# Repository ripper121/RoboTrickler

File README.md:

# RoboTrickler
 
If you like it, spend me a coffee :)

### Donation: [Paypal](https://www.paypal.com/donate/?hosted_button_id=UHZEEUSTRAF88) (paypal.me/ripper121)

### Full Manual: [Wiki](https://github.com/ripper121/RoboTrickler/wiki)

At the moment only in German, but DeepL will help you ;)

### Latest Release: [Download](https://github.com/ripper121/RoboTrickler/releases/latest)

Youtube:

# License

## creative commons

# Attribution-NonCommercial-ShareAlike 4.0 International

Creative Commons Corporation (“Creative Commons”) is not a law firm and does not provide legal services or legal advice. Distribution of Creative Commons public licenses does not create a lawyer-client or other relationship. Creative Commons makes its licenses and related information available on an “as-is” basis. Creative Commons gives no warranties regarding its licenses, any material licensed under their terms and conditions, or any related information. Creative Commons disclaims all liability for damages resulting from their use to the fullest extent possible.

### Using Creative Commons Public Licenses

Creative Commons public licenses provide a standard set of terms and conditions that creators and other rights holders may use to share original works of authorship and other material subject to copyright and certain other rights specified in the public license below. The following considerations are for informational purposes only, are not exhaustive, and do not form part of our licenses.

* __Considerations for licensors:__ Our public licenses are intended for use by those authorized to give the public permission to use material in ways otherwise restricted by copyright and certain other rights. Our licenses are irrevocable. Licensors should read and understand the terms and conditions of the license they choose before applying it. Licensors should also secure all rights necessary before applying our licenses so that the public can reuse the material as expected. Licensors should clearly mark any material not subject to the license. This includes other CC-licensed material, or material used under an exception or limitation to copyright. [More considerations for licensors](http://wiki.creativecommons.org/Considerations_for_licensors_and_licensees#Considerations_for_licensors).

* __Considerations for the public:__ By using one of our public licenses, a licensor grants the public permission to use the licensed material under specified terms and conditions. If the licensor’s permission is not necessary for any reason–for example, because of any applicable exception or limitation to copyright–then that use is not regulated by the license. Our licenses grant only permissions under copyright and certain other rights that a licensor has authority to grant. Use of the licensed material may still be restricted for other reasons, including because others have copyright or other rights in the material. A licensor may make special requests, such as asking that all changes be marked or described. Although not required by our licenses, you are encouraged to respect those requests where reasonable. [More considerations for the public](http://wiki.creativecommons.org/Considerations_for_licensors_and_licensees#Considerations_for_licensees).

## Creative Commons Attribution-NonCommercial-ShareAlike 4.0 International Public License

By exercising the Licensed Rights (defined below), You accept and agree to be bound by the terms and conditions of this Creative Commons Attribution-NonCommercial-ShareAlike 4.0 International Public License ("Public License"). To the extent this Public License may be interpreted as a contract, You are granted the Licensed Rights in consideration of Your acceptance of these terms and conditions, and the Licensor grants You such rights in consideration of benefits the Licensor receives from making the Licensed Material available under these terms and conditions.

### Section 1 – Definitions.

a. __Adapted Material__ means material subject to Copyright and Similar Rights that is derived from or based upon the Licensed Material and in which the Licensed Material is translated, altered, arranged, transformed, or otherwise modified in a manner requiring permission under the Copyright and Similar Rights held by the Licensor. For purposes of this Public License, where the Licensed Material is a musical work, performance, or sound recording, Adapted Material is always produced where the Licensed Material is synched in timed relation with a moving image.

b. __Adapter's License__ means the license You apply to Your Copyright and Similar Rights in Your contributions to Adapted Material in accordance with the terms and conditions of this Public License.

c. __BY-NC-SA Compatible License__ means a license listed at [creativecommons.org/compatiblelicenses](http://creativecommons.org/compatiblelicenses), approved by Creative Commons as essentially the equivalent of this Public License.

d. __Copyright and Similar Rights__ means copyright and/or similar rights closely related to copyright including, without limitation, performance, broadcast, sound recording, and Sui Generis Database Rights, without regard to how the rights are labeled or categorized. For purposes of this Public License, the rights specified in Section 2(b)(1)-(2) are not Copyright and Similar Rights.

e. __Effective Technological Measures__ means those measures that, in the absence of proper authority, may not be circumvented under laws fulfilling obligations under Article 11 of the WIPO Copyright Treaty adopted on December 20, 1996, and/or similar international agreements.

f. __Exceptions and Limitations__ means fair use, fair dealing, and/or any other exception or limitation to Copyright and Similar Rights that applies to Your use of the Licensed Material.

g. __License Elements__ means the license attributes listed in the name of a Creative Commons Public License. The License Elements of this Public License are Attribution, NonCommercial, and ShareAlike.

h. __Licensed Material__ means the artistic or literary work, database, or other material to which the Licensor applied this Public License.

i. __Licensed Rights__ means the rights granted to You subject to the terms and conditions of this Public License, which are limited to all Copyright and Similar Rights that apply to Your use of the Licensed Material and that the Licensor has authority to license.

j. __Licensor__ means the individual(s) or entity(ies) granting rights under this Public License.

k. __NonCommercial__ means not primarily intended for or directed towards commercial advantage or monetary compensation. For purposes of this Public License, the exchange of the Licensed Material for other material subject to Copyright and Similar Rights by digital file-sharing or similar means is NonCommercial provided there is no payment of monetary compensation in connection with the exchange.

l. __Share__ means to provide material to the public by any means or process that requires permission under the Licensed Rights, such as reproduction, public display, public performance, distribution, dissemination, communication, or importation, and to make material available to the public including in ways that members of the public may access the material from a place and at a time individually chosen by them.

m. __Sui Generis Database Rights__ means rights other than copyright resulting from Directive 96/9/EC of the European Parliament and of the Council of 11 March 1996 on the legal protection of databases, as amended and/or succeeded, as well as other essentially equivalent rights anywhere in the world.

n. __You__ means the individual or entity exercising the Licensed Rights under this Public License. Your has a corresponding meaning.

### Section 2 – Scope.

a. ___License grant.___

   1. Subject to the terms and conditions of this Public License, the Licensor hereby grants You a worldwide, royalty-free, non-sublicensable, non-exclusive, irrevocable license to exercise the Licensed Rights in the Licensed Material to:

        A. reproduce and Share the Licensed Material, in whole or in part, for NonCommercial purposes only; and

        B. produce, reproduce, and Share Adapted Material for NonCommercial purposes only.

   2. __Exceptions and Limitations.__ For the avoidance of doubt, where Exceptions and Limitations apply to Your use, this Public License does not apply, and You do not need to comply with its terms and conditions.

   3. __Term.__ The term of this Public License is specified in Section 6(a).

   4. __Media and formats; technical modifications allowed.__ The Licensor authorizes You to exercise the Licensed Rights in all media and formats whether now known or hereafter created, and to make technical modifications necessary to do so. The Licensor waives and/or agrees not to assert any right or authority to forbid You from making technical modifications necessary to exercise the Licensed Rights, including technical modifications necessary to circumvent Effective Technological Measures. For purposes of this Public License, simply making modifications authorized by this Section 2(a)(4) never produces Adapted Material.

   5. __Downstream recipients.__

        A. __Offer from the Licensor – Licensed Material.__ Every recipient of the Licensed Material automatically receives an offer from the Licensor to exercise the Licensed Rights under the terms and conditions of this Public License.

        B. __Additional offer from the Licensor – Adapted Material.__ Every recipient of Adapted Material from You automatically receives an offer from the Licensor to exercise the Licensed Rights in the Adapted Material under the conditions of the Adapter’s License You apply.

        C. __No downstream restrictions.__ You may not offer or impose any additional or different terms or conditions on, or apply any Effective Technological Measures to, the Licensed Material if doing so restricts exercise of the Licensed Rights by any recipient of the Licensed Material.

   6. __No endorsement.__ Nothing in this Public License constitutes or may be construed as permission to assert or imply that You are, or that Your use of the Licensed Material is, connected with, or sponsored, endorsed, or granted official status by, the Licensor or others designated to receive attribution as provided in Section 3(a)(1)(A)(i).

b. ___Other rights.___

   1. Moral rights, such as the right of integrity, are not licensed under this Public License, nor are publicity, privacy, and/or other similar personality rights; however, to the extent possible, the Licensor waives and/or agrees not to assert any such rights held by the Licensor to the limited extent necessary to allow You to exercise the Licensed Rights, but not otherwise.

   2. Patent and trademark rights are not licensed under this Public License.

   3. To the extent possible, the Licensor waives any right to collect royalties from You for the exercise of the Licensed Rights, whether directly or through a collecting society under any voluntary or waivable statutory or compulsory licensing scheme. In all other cases the Licensor expressly reserves any right to collect such royalties, including when the Licensed Material is used other than for NonCommercial purposes.

### Section 3 – License Conditions.

Your exercise of the Licensed Rights is expressly made subject to the following conditions.

a. ___Attribution.___

   1. If You Share the Licensed Material (including in modified form), You must:

       A. retain the following if it is supplied by the Licensor with the Licensed Material:

         i. identification of the creator(s) of the Licensed Material and any others designated to receive attribution, in any reasonable manner requested by the Licensor (including by pseudonym if designated);

         ii. a copyright notice;

         iii. a notice that refers to this Public License;

         iv. a notice that refers to the disclaimer of warranties;

         v. a URI or hyperlink to the Licensed Material to the extent reasonably practicable;

       B. indicate if You modified the Licensed Material and retain an indication of any previous modifications; and

       C. indicate the Licensed Material is licensed under this Public License, and include the text of, or the URI or hyperlink to, this Public License.

   2. You may satisfy the conditions in Section 3(a)(1) in any reasonable manner based on the medium, means, and context in which You Share the Licensed Material. For example, it may be reasonable to satisfy the conditions by providing a URI or hyperlink to a resource that includes the required information.

   3. If requested by the Licensor, You must remove any of the information required by Section 3(a)(1)(A) to the extent reasonably practicable.

b. ___ShareAlike.___

In addition to the conditions in Section 3(a), if You Share Adapted Material You produce, the following conditions also apply.

1. The Adapter’s License You apply must be a Creative Commons license with the same License Elements, this version or later, or a BY-NC-SA Compatible License.

2. You must include the text of, or the URI or hyperlink to, the Adapter's License You apply. You may satisfy this condition in any reasonable manner based on the medium, means, and context in which You Share Adapted Material.

3. You may not offer or impose any additional or different terms or conditions on, or apply any Effective Technological Measures to, Adapted Material that restrict exercise of the rights granted under the Adapter's License You apply.

### Section 4 – Sui Generis Database Rights.

Where the Licensed Rights include Sui Generis Database Rights that apply to Your use of the Licensed Material:

a. for the avoidance of doubt, Section 2(a)(1) grants You the right to extract, reuse, reproduce, and Share all or a substantial portion of the contents of the database for NonCommercial purposes only;

b. if You include all or a substantial portion of the database contents in a database in which You have Sui Generis Database Rights, then the database in which You have Sui Generis Database Rights (but not its individual contents) is Adapted Material, including for purposes of Section 3(b); and

c. You must comply with the conditions in Section 3(a) if You Share all or a substantial portion of the contents of the database.

For the avoidance of doubt, this Section 4 supplements and does not replace Your obligations under this Public License where the Licensed Rights include other Copyright and Similar Rights.

### Section 5 – Disclaimer of Warranties and Limitation of Liability.

a. __Unless otherwise separately undertaken by the Licensor, to the extent possible, the Licensor offers the Licensed Material as-is and as-available, and makes no representations or warranties of any kind concerning the Licensed Material, whether express, implied, statutory, or other. This includes, without limitation, warranties of title, merchantability, fitness for a particular purpose, non-infringement, absence of latent or other defects, accuracy, or the presence or absence of errors, whether or not known or discoverable. Where disclaimers of warranties are not allowed in full or in part, this disclaimer may not apply to You.__

b. __To the extent possible, in no event will the Licensor be liable to You on any legal theory (including, without limitation, negligence) or otherwise for any direct, special, indirect, incidental, consequential, punitive, exemplary, or other losses, costs, expenses, or damages arising out of this Public License or use of the Licensed Material, even if the Licensor has been advised of the possibility of such losses, costs, expenses, or damages. Where a limitation of liability is not allowed in full or in part, this limitation may not apply to You.__

c. The disclaimer of warranties and limitation of liability provided above shall be interpreted in a manner that, to the extent possible, most closely approximates an absolute disclaimer and waiver of all liability.

### Section 6 – Term and Termination.

a. This Public License applies for the term of the Copyright and Similar Rights licensed here. However, if You fail to comply with this Public License, then Your rights under this Public License terminate automatically.

b. Where Your right to use the Licensed Material has terminated under Section 6(a), it reinstates:

   1. automatically as of the date the violation is cured, provided it is cured within 30 days of Your discovery of the violation; or

   2. upon express reinstatement by the Licensor.

   For the avoidance of doubt, this Section 6(b) does not affect any right the Licensor may have to seek remedies for Your violations of this Public License.

c. For the avoidance of doubt, the Licensor may also offer the Licensed Material under separate terms or conditions or stop distributing the Licensed Material at any time; however, doing so will not terminate this Public License.

d. Sections 1, 5, 6, 7, and 8 survive termination of this Public License.

### Section 7 – Other Terms and Conditions.

a. The Licensor shall not be bound by any additional or different terms or conditions communicated by You unless expressly agreed.

b. Any arrangements, understandings, or agreements regarding the Licensed Material not stated herein are separate from and independent of the terms and conditions of this Public License.

### Section 8 – Interpretation.

a. For the avoidance of doubt, this Public License does not, and shall not be interpreted to, reduce, limit, restrict, or impose conditions on any use of the Licensed Material that could lawfully be made without permission under this Public License.

b. To the extent possible, if any provision of this Public License is deemed unenforceable, it shall be automatically reformed to the minimum extent necessary to make it enforceable. If the provision cannot be reformed, it shall be severed from this Public License without affecting the enforceability of the remaining terms and conditions.

c. No term or condition of this Public License will be waived and no failure to comply consented to unless expressly agreed to by the Licensor.

d. Nothing in this Public License constitutes or may be interpreted as a limitation upon, or waiver of, any privileges and immunities that apply to the Licensor or You, including from the legal processes of any jurisdiction or authority.

> Creative Commons is not a party to its public licenses. Notwithstanding, Creative Commons may elect to apply one of its public licenses to material it publishes and in those instances will be considered the “Licensor.” The text of the Creative Commons public licenses is dedicated to the public domain under the CC0 Public Domain Dedication. Except for the limited purpose of indicating that material is shared under a Creative Commons public license or as otherwise permitted by the Creative Commons policies published at creativecommons.org/policies, Creative Commons does not authorize the use of the trademark “Creative Commons” or any other trademark or logo of Creative Commons without its prior written consent including, without limitation, in connection with any unauthorized modifications to any of its public licenses or any other arrangements, understandings, or agreements concerning use of licensed material. For the avoidance of doubt, this paragraph does not form part of the public licenses.
>
> Creative Commons may be contacted at creativecommons.org

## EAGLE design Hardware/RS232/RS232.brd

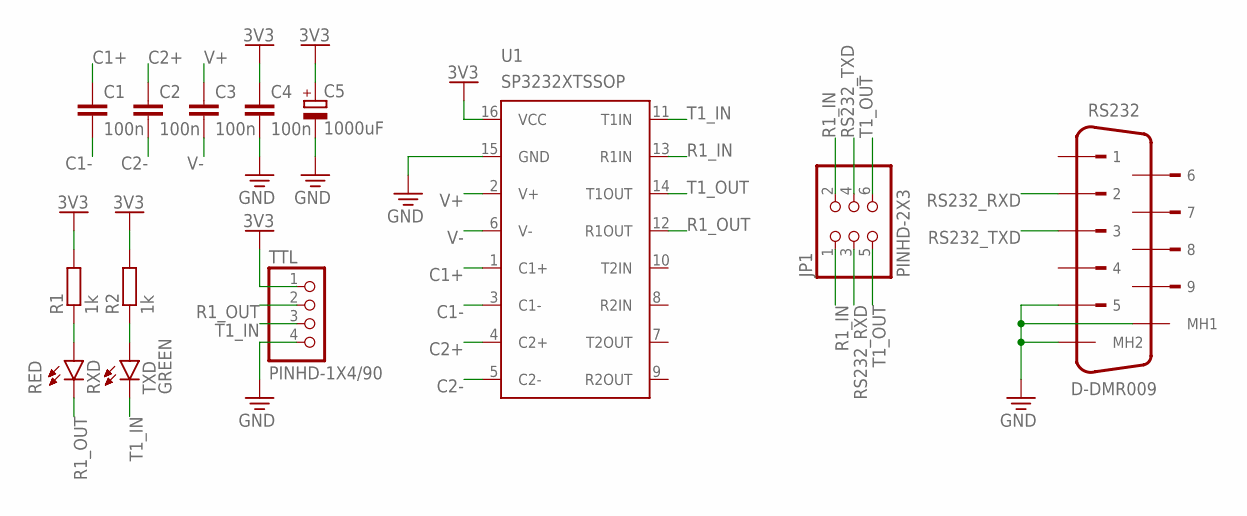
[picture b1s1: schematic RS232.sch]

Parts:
C1, C2, C3, C4: 100n; C0402
C5: 1000uF; 140CLH-1010
JP1: PINHD-2X3; 2X03
R1, R2: 1k; R0402
RS232: D-DMR009; 5747840-4
RXD: RED; CHIP-LED0603
TTL: PINHD-1X4/90; 1X04/90
TXD: GREEN; CHIP-LED0603
U1: SP3232XTSSOP; TSSOP16

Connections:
3V3: C4.1, C5.+, R1.2, R2.2, TTL.1, U1.16 (VCC)
C1+: C1.1, U1.1 (C1+)
C1-: C1.2, U1.3 (C1-)
C2+: C2.1, U1.4 (C2+)
C2-: C2.2, U1.5 (C2-)
GND: C4.2, C5.-, RS232.5, RS232.MH1 (MH2), RS232.MH2 (MH1), TTL.4, U1.15 (GND)
unnamed: R1.1, RXD.A
unnamed: R2.1, TXD.A
R1_IN: JP1.1, JP1.2, U1.13 (R1IN)
R1_OUT: RXD.C, TTL.2, U1.12 (R1OUT)
RS232_RXD: JP1.3, RS232.2
RS232_TXD: JP1.4, RS232.3
T1_IN: TTL.3, TXD.C, U1.11 (T1IN)
T1_OUT: JP1.5, JP1.6, U1.14 (T1OUT)
V+: C3.1, U1.2 (V+)
V-: C3.2, U1.6 (V-)

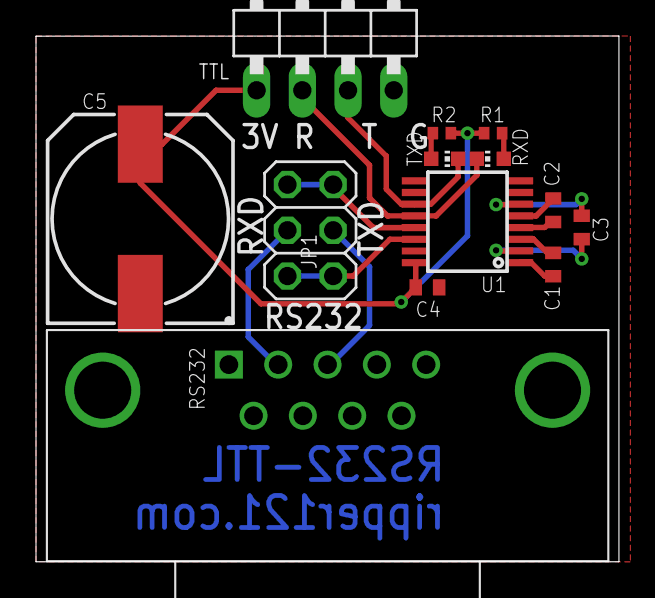
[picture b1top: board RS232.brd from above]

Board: 2 copper layers, 32.4 x 29.2 mm, 13 parts (0 on the bottom side), 16 nets.

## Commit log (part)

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2023-11-20 License rename
2023-11-21 Added StaticIP Option, Typo Fix
2023-11-21 Added PID Prototype
2023-11-21 Trickler Options for PID
2023-11-22 Working PID and StaticIP
2023-11-22 Version 2.00
2023-11-24 Lvgl & Powder Load on Save
2023-11-24 Tracker
2023-11-24 DNS Server
2023-11-24 Cleanup
2023-11-24 Running Display in own Core
2023-11-24 New UI Ready
2023-11-28 UI Update
2023-12-01 UI Ready 2 Use
2023-12-01 ui_TextAreaInfo Crash
    Reduce the shown characters in ui_TextAreaInfo to prevent a crash
2023-12-01 Update Libs
2023-12-01 Version 2.00 with new UI
2023-12-05 Removed Roller
2023-12-06 cleanup / alarm threshold
2023-12-07 AlarmThreshold & Target Threshold
2023-12-07 Updated html Generators
2023-12-07 Robo-Trickler v2.00
    - New UI
    - target weight tolerance
    - alarm for over trickle
    - many small improvements
    !!! If you come from a Firmware <2.00 you need to flash the new Firmware via USB !!!
2023-12-07 RoboTrickler_v2.00
2023-12-07 fixed config template
2023-12-07 Fixed Typo, Alarm Text Red
2023-12-13 Lib Update, Tolerance and Alarm moved to Profiles
2023-12-13 Some Fixes
2023-12-13 Improved Profile Generator, FW Check
2023-12-13 Robo-Trickler v2.01
2023-12-16 SD-Files Fixes
2023-12-20 Images
2023-12-21 updated binarys
2024-01-06 Update 3D Files & RS232
2024-01-09 Webserver Handle to display Task
2024-01-09 RS232
2024-01-12 Fixed RS232
2024-01-12 Profiel Update
2024-01-15 Added RS60 & profilGenerator Fixes
2024-01-16 ProfilEditor & SD-File fixes
2024-01-16 Create_SD_Card.sh
    For Mac and Linux
2024-01-17 RS232 & Powder List
2024-01-18 SD-File Update
2024-01-18 Profiles
2024-01-21 Powder List & Setup Wizzard
2024-01-21 Changed Adapter_50mm.stl
2024-02-05 3D Files optimized for Bambu Lab P1S
2024-02-17 Moved sample profiles
2024-02-25 Update 3D Files
2024-02-26 New 3D Files & AVG Profile
2024-02-26 FW Improvements & New 3D Files
    FW Improvements :
    - added Start via Webserver
    - added Stop via Webserver
    - fixed set Target Weight via Webserver
    3D Files:
    - New Riser
2024-02-27 Trickler via WebUI
2024-02-29 3D File Improved
2024-03-01 Cleanup & New Trickler Web Functions.
2024-03-05 v2.03 & 25mm Trickler
2024-03-06 Get Weight always from Scale
2024-03-15 feat: Add screen rotation config
2024-03-16 Small Display FIx
2024-03-16 Revert "Merge branch 'main' of https://github.com/ripper121/RoboTrickler"
    This reverts commit a99646fef7c1d2a99d02272bfcd114e46a468bf8, reversing
    changes made to fb8cf387e7d8991dbf83e06e69b2c1b51f5d2590.
2024-03-18 25mm Ready to use
2024-03-28 Screen FIx
2024-03-28 old calc
2024-04-07 RS232 Update
2024-04-09 Small fix
2024-04-29 Custom Protocol Code for Scale
2024-05-12 Awacs Mod
2024-05-15 Added acceleration
2024-05-27 acceleration & fw_check, some fixes
2024-05-28 Profile Improvments
    - Max 15 Profile Entrys
2024-05-31 4mm Holes Stand
2024-06-03 Latest Config and new Binarys
2024-06-07 Auto calc of first throw
2024-06-16 small fixes
2024-06-16 RS232 Cleanup
2024-06-25 ConfigGenerator & Max Target
2024-07-09 fixes
2024-07-11 Fixed Tolerance, Added Color to Weight
2024-07-11 Lib Update
2024-07-13 2 Trickler Fix
2024-07-16 Cleaner File Layout on SD Card
2024-07-18 New Trickler Designe & 70 mm Powder Tank
2024-08-07 New 3D Files & SD-Card Image
2024-08-29 added Docs
2024-10-08 Fixed TargetWeight Save Bug
2024-10-09 Power Measure
2024-11-29 3D File Mods
2024-12-03 BugFix
    If the profile which was defined in the config.txt is not found, calibrate.txt will be used.
2024-12-03 Update ArduinoJson Lib
2024-12-27 Protocol readout fix, calibration fix, firstThrow fix
2025-01-06 v 2.07
2025-01-12 TargetWeight Fix
2025-01-12 renane
2025-01-27 Enclosure for Control Unit by marwaw-ops
    https://github.com/ripper121/RoboTrickler/issues/3
    https://github.com/marwaw-ops
2025-03-18 Better Error Messages
2025-04-08 2.08
2025-06-23 New 3D Files
2025-08-30 New RS232
2026-03-29 ESP-IDF Version
2026-03-29 ESP-IDF
2026-03-29 Instant Stopp
2026-03-30 ESP-IDF remove use of Arduino Libs Stage 1
2026-03-30 improvements
2026-04-10 Clean Compile
2026-04-10 Removed Gestures
2026-04-11 Version 2.09
    No Touch Gestures
2026-04-22 IDF Sample project
2026-04-28 IDF Version beta
2026-04-28 removed PID and Logger
2026-04-29 removed microstep setting
2026-04-29 auto calibration
2026-04-30 new Profile
2026-04-30 idf template
2026-04-30 replaced stepper lib
2026-04-30 Update LVGL lib to latest
2026-04-30 ram fix
2026-04-30 removed wdt
2026-04-30 Languages
2026-04-30 v2.10
2026-04-30 init
2026-05-04 FW Update URL
2026-05-11 New Enclosure
2026-05-11 v2.11 pre
2026-05-11 ai-cleanup
2026-05-11 ai-fixes
2026-05-12 general actuator
2026-05-12 manual.md update
2026-05-26 removed conversation to degrees
2026-05-26 removed reverse
2026-05-26 fix: the device's web interface makes fetch() calls ... in trickler.html
    The device's web interface makes fetch() calls to configuration endpoints (/getTarget, /getProfile) without any authentication tokens, session cookies, or authorization headers
2026-05-26 cleanup & fixes
2026-05-27 startAtZero
2026-05-28 wifi and webserver fixes
2026-06-04 RS232 Fixes
2026-06-04 trickle counter
2026-06-04 global Trickle counter & reboot button for editor
2026-06-04 update changelog and manual
2026-06-04 Release 2.11
2026-06-05 UI Project Update
2026-06-05 Logo
2026-06-05 FW Check
2026-06-05 SD-Files Update
2026-06-05 update SD Files
2026-06-08 Non Blocking Wifi, CUSTOM TX RX Log
2026-06-08 gg_emu req/sec
2026-06-08 Debug Off
2026-06-09 Screenshot
2026-06-09 lang fix
2026-06-09 fix lang, removed screenshot
2026-06-09 Screenshot Web
2026-06-09 reboot web ui fix
2026-06-10 new compile
2026-06-10 better logo
2026-06-10 removed idf
2026-06-10 fix A&D
2026-06-10 debug level
2026-06-10 extract tar
2026-06-11 Revert "extract tar"
    This reverts commit 2e3bc0cf48383190ceccf7476af0e26900403ac9.
2026-06-11 removed DownloadSdFiles
2026-06-11 new bin
2026-06-11 ino reorganized
2026-06-11 Function, Variable Renaming and new Comments
2026-06-11 WEIGHT_SCALE_FACTOR
2026-06-11 state machine
2026-06-11 CAD Update
2026-06-11 KERN-ABS
2026-06-11 Measurment Counter Display
2026-06-11 Tune Button
2026-06-11 UI cleanup & Tuning
2026-06-12 LVGL conform UI Dialogs
2026-06-12 Added LVGL Message Boxes
2026-06-12 reverted LVGL Messagebox, back to my impl
2026-06-12 fixed Heap overflows
2026-06-12 trickle.html
2026-06-12 UI Fixes
2026-06-12 disable wdt
2026-06-12 dialog crash fixed
2026-06-12 change fonts
2026-06-13 Release 2.12
2026-06-13 First No SD Version
2026-06-13 NetworkClientSecure removed
2026-06-13 no special AP Portal
2026-06-13 QR AP Code
2026-06-13 RC 1.0
2026-06-13 SD & LittleFs
2026-06-13 better SD / FS info
2026-06-13 8MB Flash, Lang, SD Update
2026-06-13 SD Update order First
2026-06-13 Latest Bin Files
2026-06-13 Version 2.13 LittleFS Flash
2026-06-13 SD Bin files
2026-06-13 todo
2026-06-13 manual.md
2026-06-14 profile tweaks
2026-06-14 New features
2026-06-14 optimisation
2026-06-14 Sync and change Protocol via UI
2026-06-14 Moved buttons
2026-06-14 Sync Flash SD
2026-06-14 Wifi QR Code, Wifi Toggle
2026-06-14 QR Code pos
2026-06-14 UI Dialog Bug Fixes
2026-06-14 UI fixes
    Completed the deep UI pass and fixed:
    Stale dialogs during web-triggered actions.
    False running-state button after failed startup.
    Repeated web starts and profile changes while running.
    Dialog and long-label overflow.
    Invalid-profile message clipping.
2026-06-14 2.13 Release Bin
2026-06-14 manual update
2026-06-15 Profile generator removed, update Profil editor
2026-06-15 sd update info in display
2026-06-15 offline SD start.html fix
2026-06-17 CZD-Port
2026-06-17 SD-Card Speed fix, LittleFS space save
2026-06-17 user tracker
2026-06-17 removed ut
2026-06-17 make MOTOR_REV_STEPS configurable through config.json
2026-06-17 latest bin
2026-06-17 fix: display negative scale weights instead of NaN
    weight < 0.0 is a normal condition (tared scale drifting negative,
    empty weighing cup, etc.). Using -1.0 as the "no reading" sentinel
    conflated this with real negative readings.
    Replace the -1.0 sentinel with NAN so isfinite() is the sole guard
    in setWeightLabel. The trickler arithmetic is unaffected: all weight
    comparisons in trickler_runtime.ino are reached only via handleNewWeight(),
2026-06-18 Display Negativ Values, SD-Card Timing
2026-06-18 pre Release 2.14
2026-06-18 Switched from unitsPerThrow to unitsPerRev
2026-06-18 Max Profile Info
2026-06-19 Config and Profile Load optimisation
2026-06-19 html style and translations
2026-06-19 renamed speed to rpm
2026-06-19 profile list fix
2026-06-23 naming audit
2026-06-23 better struct of json files
2026-06-23 steppers to stepper
2026-06-23 Units / Rev to weight / rev
2026-06-23 Better Naming
2026-06-23 naming
2026-06-23 added agents back
2026-06-26 New Bin Files and Manual.pdf
